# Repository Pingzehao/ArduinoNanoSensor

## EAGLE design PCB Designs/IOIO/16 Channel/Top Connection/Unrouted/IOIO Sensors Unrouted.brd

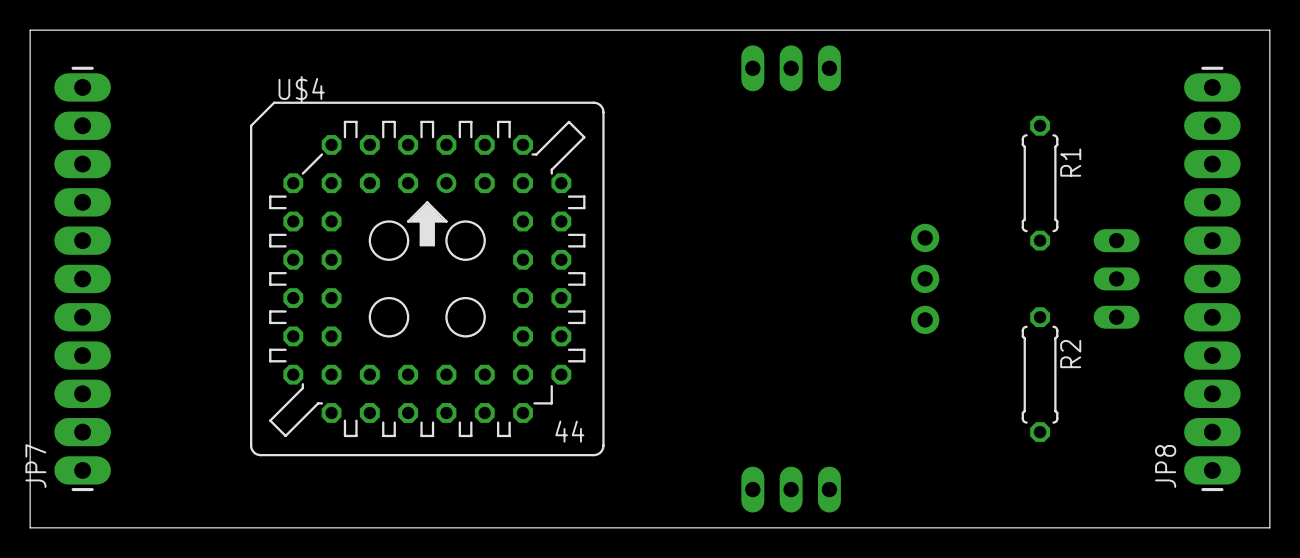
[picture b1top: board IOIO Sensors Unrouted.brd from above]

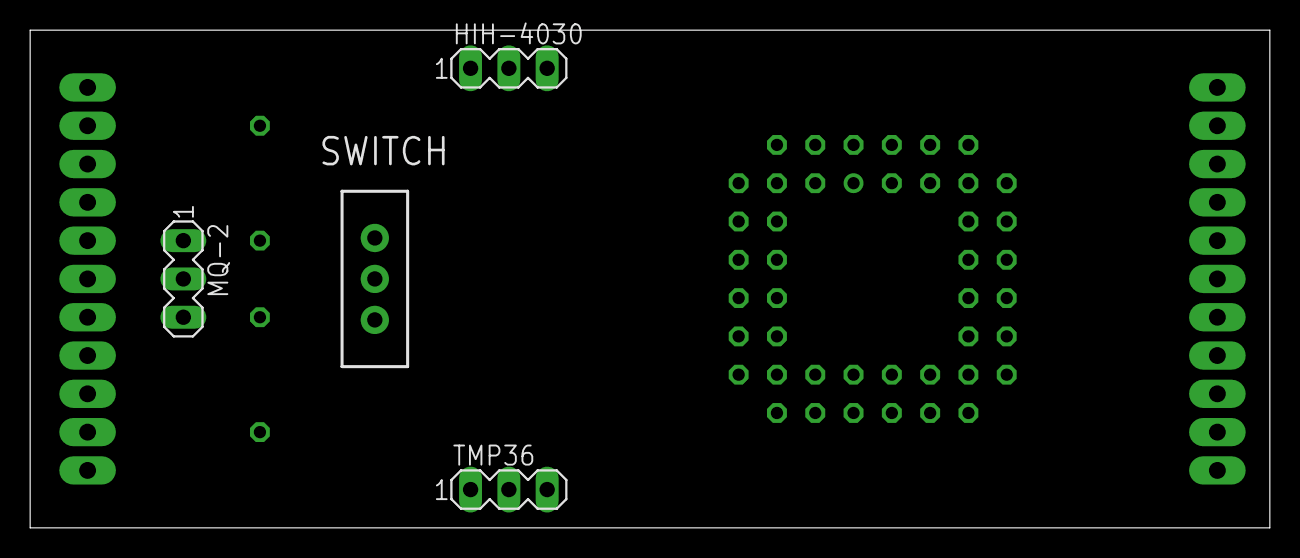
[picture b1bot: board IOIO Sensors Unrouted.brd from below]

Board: 2 copper layers, 82.2 x 33.0 mm, 9 parts (4 on the bottom side), 24 nets, no tracks yet.

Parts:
HIH-4030: MA03-1
JP7, JP8: M11LONGPADS; 1X11_LONGPADS
MQ-2: MA03-1
R1, R2: 10k; 0207/7
SWITCH: SWITCH-SPDT_LOCK.007S
TMP36: MA03-1
U$4: S44

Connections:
3.3V: HIH-4030.3, JP7.2
5V: JP7.1, SWITCH.2, TMP36.3
GND: HIH-4030.1, JP7.3, MQ-2.1, R2.2, TMP36.1, U$4.2, U$4.4, U$4.6, U$4.8, U$4.13, U$4.15, U$4.17, U$4.19, U$4.24, U$4.26, U$4.28, U$4.30, U$4.35, U$4.37, U$4.39, U$4.41
MQ2OUT: MQ-2.3, R1.1
MUX1: JP7.4, U$4.1
MUX2: JP7.5, U$4.3
MUX3: JP7.6, U$4.5
MUX4: JP7.7, U$4.7
MUX5: JP7.8, U$4.12
MUX6: JP7.9, U$4.14
MUX7: JP7.10, U$4.16
MUX8: JP7.11, U$4.18
MUX9: JP8.1, U$4.23
MUX10: JP8.2, U$4.25
MUX11: JP8.3, U$4.27
MUX12: JP8.4, U$4.29
MUX13: JP8.5, U$4.34
MUX14: JP8.6, U$4.36
MUX15: JP8.7, U$4.38
MUX16: JP8.8, U$4.40
PIN32: JP8.9, R1.2, R2.1
PIN33: HIH-4030.2, JP8.10
PIN34: JP8.11, TMP36.2
SWITCHON: MQ-2.2, SWITCH.3
